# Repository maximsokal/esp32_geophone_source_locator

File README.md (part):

# ESP32 Geophone Source Locator

ESP32-S3 diploma prototype for seismic search under rubble. The firmware acquires multiple geophone channels simultaneously, stores object/measurement data on microSD, exposes a local web interface, provides a local TFT UI, and now contains a reusable 3D TDOA geometry solver for the later localization pipeline.

The project targets **ESP-IDF v5.5.4** on an ESP32-S3 N16R8 board.

For the component/runtime design, task ownership and extension rules, see [ARCHITECTURE.md](ARCHITECTURE.md).

Structural code search and linting use [ast-grep](docs/ast-grep.md).

## Current hardware architecture

### ESP32-S3

The controller is an ESP32-S3 with 16 MB flash and 8 MB octal PSRAM.

PSRAM runs at 80 MHz. If the board is unstable (random crashes after a ~20 °C temperature change or boot failures), revert to `CONFIG_SPIRAM_SPEED_40M`; HIL validation is required.

GPIO33-GPIO37 are occupied by octal PSRAM internally and are intentionally not assigned to application peripherals.

### SPI2: UI and storage

SPI2 is shared only by the TFT and microSD card:

| Signal | ESP32-S3 GPIO |
| --- | ---: |
| MOSI | 11 |
| SCLK | 12 |
| MISO | 13 |
| TFT CS | 14 |
| TFT DC | 15 |
| TFT RESET | 16 |
| microSD CS | 17 |

The current firmware sets the microSD SPI runtime ceiling to **20 MHz** (`SDMMC_FREQ_DEFAULT`); discovery starts at 400 kHz. This is the configured ceiling, not a claim that the present wiring has been physically validated at that rate.

### SPI3: dedicated AD7606 acquisition bus

AD7606 is isolated from the display/storage bus and owns SPI3:

| AD7606 signal | ESP32-S3 GPIO |
| --- | ---: |
| DOUTA / DB7 / MISO | 39 |
| RD / SCLK | 40 |
| CS | 41 |
| CONVST A + CONVST B | 42 |
| BUSY | 47 |
| RST | 2 |

AD7606 serial mode is read-only, therefore SPI3 MOSI is unused. A 10 kOhm pull-up is used on AD7606 CS.

Current AD7606 board configuration:

- RANGE low: +/-5 V input range;
- OS0/OS1/OS2 low: no hardware oversampling;
- 8 simultaneous channels;
- SPI mode 2;
- 1 MHz SPI clock;
- default acquisition rate: 500 Hz.

The first four AD7606 channels currently feed the application seismic ring buffer. All eight channels are read on every conversion and are available to the local TFT diagnostics UI.

### Other current GPIO assignments

| Function | GPIO |
| --- | ---: |
| Analog keypad KS0466 | 8 |
| Pololu power-off control | 18 |
| External power-button sense | 21 |

GPIO1 is reserved by the existing divider/bench wiring and must not be reused for AD7606.

### nRF54L15 subproject

`nRF54L15/` is an independent PlatformIO + Zephyr project for all XIAO
nRF54L15 nodes. It has one production source tree, one production environment
and one firmware binary; runtime topology and Bluetooth initiator/reflector
roles do not create central/remote builds. The main node is on the ESP32-S3
upstream I2C bus; remote nodes are behind TCA9548A channels. Each remote nRF
locally aggregates its GY-BMI160 and BME280 on the second XIAO I2C pair
(`D11/P0.03` SCL, `D12/P0.04` SDA), powered from XIAO `3V3_OUT`. These local
sensors are not direct ESP32/TCA devices. RJ45 pin 2 (+3.3 V) is reserved/NC
and must not be tied to `3V3_OUT`.

The installed boards are the **plain XIAO nRF54L15, not the Sense variant**,
so they have no built-in IMU. Each remote geophone uses an external
**GY-BMI160** and BME280 on the XIAO's private second I2C bus: `D11/P0.03` is
SCL and `D12/P0.04` is SDA. The upstream ESP32/TCA bus remains on
`D4/P1.10` SDA and `D5/P1.11` SCL. The main-enclosure nRF54L15 does not
require the remote-only sensor assembly.

The REMOTE logger LEDs show GREEN while READY when no fault has latched; GREEN
means “no latched fault,” not that sensor preparation has completed. An
unattempted sensor is pending, while a failed BMI160 or required BME280 init is
an immediate ERROR. Runtime IMU/ENV fault bits count only after that sensor is
READY. WARNING must persist for 2000 ms before YELLOW latches; ERROR/FATAL is
immediate, and latches clear only on reset. `LOG_RING_LOSS` latches WARNING
when `overwritten_total > 0` (internal logger losses also map to WARNING). The
128-record ring can overwrite during a bench run without an ESP32 collector,
producing a latched YELLOW; this is expected bench behavior.

The authoritative topology, local sensor/power contract, external
GY-BMI160/verticality contract, Channel Sounding role rotation and remote LED
pinout are in
[`ARCHITECTURE.md`](ARCHITECTURE.md). The future nRF implementation and
testing task is [`docs/nrf54l15-test-task.md`](docs/nrf54l15-test-task.md).

## UI architecture

The TFT UI uses **LVGL 9** through Espressif's official **esp_lvgl_port** integration. The display component is limited to the physical `esp_lcd` / ILI9341 layer; widgets, text, QR rendering, navigation, refresh timing and buffering belong to LVGL.

Managed dependencies are pinned through the ESP-IDF Component Manager:

- `espressif/esp_lcd_ili9341 ^2.0.2`;
- `espressif/esp_lvgl_port ^2.9.0`;
- `lvgl/lvgl ^9.5.0`;
- `espressif/button 4.2.0` for the keypad and power-button adapters;
- `espressif/i2c_bus 1.5.2` for the shared INA3221 sensor bus;
- `espressif/led_indicator 2.1.2` as the disabled, board-wiring-gated status backend;
- `espressif/esp-dsp 1.8.2` for the task-free measured-signal foundation;
- optional `espressif/esp_insights 1.3.4`, disabled in the baseline image.

The previous project-local 5x7 bitmap font and custom text-rendering stack are no longer part of the active display architecture.

The LVGL handler task is pinned to **Core 0**. The five-button analog keypad
uses official ADC Button objects over the existing ADC1 owner, and the GPIO21
power input uses the official GPIO Button object with external pull circuitry.
Both adapters publish to the dedicated ESP-IDF `APP_EVENT` user loop; the UI
subscriber only queues events and applies them from the existing LVGL timer.
The event loop contract is documented in
[`ARCHITECTURE.md`](ARCHITECTURE.md), and the before/after resource snapshot is
in [`docs/architecture-refactor-baseline-2026-09-12.md`](docs/architecture-refactor-baseline-2026-09-12.md).

Screen behavior is registered through one `ui_screen_driver_t` table. Open/render/key/refresh behavior and the Home menu label therefore have one source of truth instead of duplicated enum/switch routing.

Current screens:

- Home;
- Objects;
- Measurements;
- Storage;
- Wi-Fi / Web;
- System.

The **Measurements** screen is live, not a placeholder. For the AD7606 build it displays:

- acquisition source and RUN/STOP state;
- sample rate and channel count;
- real-time core assignment;
- SPI3 transport, SPI mode and bus clock;
- configured +/-5 V range and hardware oversampling ratio;
- successful sample count, read errors and consecutive failures;
- age of the last simultaneous sample;
- live V1..V8 values in mV.

The UI consumes a read-only `seismic_acquisition_snapshot_t`; it does not access AD7606 GPIO or SPI functions directly.

## CPU/task policy

Application-owned tasks are split by role.

### Core 0 - services

- LVGL handler and bounded UI event application;
- ESP-IDF `APP_EVENT` user loop and official Button service;
- object service;
- storage service;
- Wi-Fi/HTTP-facing application work.

### Core 1 - real-time side

- AD7606 acquisition;
- synthetic seismic test source;
- future signal preprocessing / event detection;
- future continuous localization worker if required.

All application task priorities, stacks and core assignments are centralized in `components/app_config/include/app_task_config.h`.

The AD7606 task initializes and owns SPI3 on Core 1 so the dedicated acquisition bus and its interrupt affinity remain on the real-time side.

## Seismic acquisition pipeline

For the AD7606 source:

```text
geophone
   -> low-noise analog amplifier/filter
   -> AD7606 simultaneous analog inputs
   -> CONVST
   -> timestamp captured at the sampling event
   -> BUSY completion
   -> SPI3 read of V1..V8
   -> acquisition diagnostics snapshot
   -> seismic ring buffer
   -> web / recording / future signal processing
```

The frame timestamp is captured immediately after the CONVST rising edge, not after BUSY handling and SPI transfer.

The seismic ring buffer uses short metadata critical sections plus per-slot publication sequencing. HTTP snapshots do not hold a long mutex while copying hundreds of waveform frames, so a slow web reader does not block the acquisition producer for the duration of the copy.

## Acquisition source interface

The source is selected at build time in `menuconfig`:

- `AD7606 SPI acquisition` - normal hardware path;
- `Synthetic test waveform` - software-only waveform source.

Each backend implements the same private `seismic_source_driver_t` interface. The acquisition orchestrator itself is backend-agnostic; compile-time selection is isolated in the source registry. Runtime source switching is intentionally not exposed yet.

Current backend files:

- `seismic_source_ad7606.c`;
- `seismic_source_test.c`.

Adding a new source should add a descriptor and registry entry rather than adding source-specific branches to `seismic_acquisition.c`.

## TDOA localization component

The repository now contains an independent `localization` component with a reusable 3D TDOA solver:

```c
esp_err_t localization_tdoa_solve(...);
```

It accepts:

- 4..8 sensor positions in meters;
- one arrival timestamp per sensor for the same detected event;
- a propagation speed in m/s;
- an optional initial source-position guess.

It returns:

- estimated `(x, y, z)` source position;
- estimated emission time;
- RMS timing residual;
- iteration count;
- convergence status.

The solver rejects degenerate/coplanar 3D sensor geometry and uses damped nonlinear least-squares iterations.

Beside it, `localization_velocity_free` provides three methods that estimate the event's own velocity: **TDCAS** (P picks, 6 sensors or 5 on a flat array), **PSAFUVS** (P and S picks, 4 flat sensors suffice) and **SUEA** (shortest travel paths around empty areas). "Calculate source" runs all of them; when the session has a registered 3D scan, their scan-constrained variants use the scan's empty (FREE) and filled (OCCUPIED) space. See [ARCHITECTURE.md](ARCHITECTURE.md#velocity-free-methods-and-the-3d-scans-emptyfilled-space).

`localization_extended` adds five more: **cross-correlation TDOA** over every pod pair, a **robust** outlier-rejecting fit, **PSP** (P-TDOA and S-P jointly), **eikonal** travel times that go around the scan's voids (plus tomography from calibration hits), and a **Bayesian** posterior that reports a 90% credible region instead of a bare point. With four flat pods, place them off a common circle (not in a rectangle) if you want the velocity-free methods. See [ARCHITECTURE.md](ARCHITECTURE.md#extended-methods-waveform-delays-robust-fits-p-s-eikonal-posterior).

**Important:** this does not mean the end-to-end locator is finished. The firmware still needs a validated preprocessing/event-detection stage that converts raw geophone data into reliable per-channel arrival timestamps. The propagation speed also cannot be hard-coded as a universal constant for heterogeneous rubble; `localization_default_config()` deliberately leaves `propagation_speed_mps` unset so the caller must provide a measured or modelled value.

Planned end-to-end path:

```text
AD7606 frames
   -> filtering / preprocessing
   -> event detection
   -> per-channel arrival-time picking
   -> sensor position / height data
   -> propagation model
   -> localization_tdoa_solve()
   -> source position + residual / quality
```

## Current timing limitation

Timestamp placement is already correct: timestamps represent CONVST, not later SPI completion.

The periodic trigger is still initiated by `esp_timer` + task notification. That is acceptable for the current bench stage, but it is not claimed to be the final deterministic sampling architecture. If the later TDOA error budget shows scheduler/trigger jitter to be significant, CONVST timing must move to a hardware-timed path rather than merely changing where software reads a timestamp.

## Storage and safe shutdown

Object and measurement state is stored under `/sdcard/geolocator`.

The shutdown sequence stops producers/services before cutting power:

```text
official Button adapters / shutdown latch
-> INA3221 monitor
-> shared sensor_bus / I2C0 release
-> measurement service / recorder finalization (LVGL guard still alive)
-> APP_EVENT UI subscriber / LVGL port
-> storage service
-> object service
-> seismic acquisition
-> HTTP / Wi-Fi
-> storage manager
-> SD unmount
-> display disable/deinit
-> power-off pulse
```

The SD handle is cleared only after successful FAT unmount. If unmount fails, software state still reflects that the card handle is present.

The TFT Storage screen requires a second confirmation before application-data erase is started.

## Web interface

The firmware starts a local HTTPS server on port 443 (`https://geolocator.local/`) and exposes device/seismic APIs including:

- `/api/status`
- `/api/seismic`

`/api/seismic` can return recent waveform frames without holding the acquisition producer behind a long reader-side copy.

The web component exposes only `include/web_server.h` publicly. Internal routes, JSON helpers, setup parsing and static-asset declarations share one private `web_server_internal.h` instead of a separate private header for every `.c` file.

## Build

For local firmware tests, the risk-based coverage plan and host/target verification boundaries, see [docs/firmware-test-plan.md](docs/firmware-test-plan.md). The project-wide validation contract, including the staged nRF54L15 software/HIL gates, is [docs/local-verification.md](docs/local-verification.md).

The sensor input/output map and its offline executable checks are in [docs/sensor-signals.md](docs/sensor-signals.md): `python tools/run_sensor_signal_checks.py`.

Install ESP-IDF v5.5.4 and open an ESP-IDF terminal in the repository directory.

When managed dependencies change:

```powershell
idf.py reconfigure
```

Build:

```powershell
idf.py build
```

Select another seismic backend:

```powershell
idf.py menuconfig
```

Then open **Seismic Acquisition** and select the required source.

## Flash and monitor

For repeatable local verification, use the tasks in `.vscode/tasks.json`:

* `Tests: nRF54L15` launches the isolated path-safe PlatformIO/Zephyr automatic
  software-test action through `nRF54L15/pio.ps1` without uploading a test
  image. Only explicitly qualified `test_sw_*` suites belong to this path.
* `nRF54L15: Flash firmware` builds and uploads the nRF54L15 image through
  `nRF54L15/pio.ps1`; it is a physical-board action and is not part of
  `Tests: All (no flash)`.
* `Tests: All (no flash)` is the no-flash project-wide entry point. It includes
  the nRF54L15 wrapper build and only qualified nRF software/native tests; an
  empty current `test_sw_*` surface is reported as `SKIPPED`. Physical nRF
  target/HIL suites are excluded even though PlatformIO also supports embedded
  tests.
* `ESP: Unity tests (flash COM4 + logs COM6)` runs the target Unity cases with
  a live COM4 preflight, an explicit test-app flash, and a bounded COM6 log
  capture.
* `ESP: Production pipeline HIL (COM4 + COM6)` builds the production image,
  prompts for the HTTPS base URL and an existing object ID, then runs the live
  acquisition/recorder/API gate with explicit COM4 flash and COM6 logging.
* `ESP: Flash production (COM4)` and `ESP: Monitor logs (COM6)` remain separate
  tasks for production firmware, each with its matching live-port preflight.
* `ESP-IDF: Monitor + Save Logs` lets you choose a COM port and keeps one UTF-8
  capture file in `logs/esp32/` while waiting through startup port errors and
  USB reconnects. `RUNNING` appears after UART data arrives. Stop the active
  monitor with `Ctrl+]`, or use `Ctrl+C` while it is retrying the connection.

For the keypad ADC/timer-task watchlist, use the dedicated opt-in procedure in
[docs/keypad-adc-timing-hil.md](docs/keypad-adc-timing-hil.md). It measures
broker snapshot `min/avg/p95/max` and shared `ESP_TIMER_TASK` dispatch lateness
for separate AD7606 500 Hz windows; it does not change the
production defaults. Its `KEYPAD_TIMING_TELEMETRY_RESULT` confirms only
telemetry validity and is independent of the physical keypad condition;
`PHYSICAL_CONDITION` and `KEYPAD_TIMING_RUN_RESULT` report the separate HIL
gate. Performance acceptance remains `NOT_ESTABLISHED` until real-board
baselines define thresholds.

The host contracts cover the AD7606 DMA configuration; the production HIL
runner reports AD7606 startup, configured-rate frame cadence, recorder/session
metadata, exact seismic channel IDs and bounded timestamp jitter,
`/api/seismic`/`/api/status` checks (including zero AD7606 read errors and
consecutive failures) and advancing FreeRTOS heartbeats for the
acquisition, recorder and UI loops. The official Button component owns input
sampling/debounce; its physical delivery and electrical behavior are checked
separately during HIL. During recording it
also requires acquisition and recorder progress to advance. It uses the device
monotonic `runtime.now_ms` to reject task heartbeats older than the configured
`-MaxTaskHeartbeatAgeMs` (default 1000 ms). TFT pixels and
keypad/power-button responsiveness still require a human observation during the
live Measurements run; use `-RequireFullPipeline` so missing API, SD or physical
evidence is reported as `BLOCKED` instead of being mistaken for a complete pass.
After observing the live screen, keypad navigation and ordered shutdown, repeat
the explicit command with `-ConfirmTftRendering -ConfirmKeypadResponsive
-ConfirmPowerButtonResponsive` to record those three manual attestations as
`PASS`.

Use the board programming port for flashing:

```powershell
idf.py -p COM4 flash
```

In the current bench setup an external USB-to-TTL adapter can be used as a passive UART monitor while the device runs from the 2x18650 power system. The external adapter must not power the ESP32 board.

Typical passive monitor wiring:

```text
ESP32 GPIO43 TX -> USB-TTL RXD
ESP32 GND       -> USB-TTL GND
```

USB-TTL TXD and power pins are not required for log-only monitoring.

Example:

```powershell
idf.py -p COM6 monitor
```

COM numbers are development-machine specific.

## Hardware bring-up checks

A normal AD7606 start should contain messages equivalent to:

```text
AD7606_DRIVER: GPIO configured: RESET=2 CONVST=42 BUSY=47 CS=41
AD7606_DRIVER: Initializing dedicated SPI3: MISO=39 SCLK=40
AD7606_DRIVER: SPI3 initialized successfully: DMA=auto (SPI_DMA_CH_AUTO)
AD7606_DRIVER: Self-test conversion + SPI read OK
AD7606_ACQ: Started: 500 Hz, 8 channels, SPI3 dedicated, core=1
```

For a known approximately 1.6 V divider connected to V8, a representative reading is around:

```text
raw=[...,10500]
mV=[...,1602]
```

The same V8 value should appear on the LVGL Measurements screen. Exact values depend on the measured supply/reference/input voltage and must not be treated as a calibration result.

## Open-source components and original work

### Open-source components

#### ESP32-S3 and ESP-IDF components

| Component | Version | SPDX license | Source | Usage |
| --- | --- | --- | --- | --- |
| ESP-IDF | 5.5.4 | [Apache-2.0](https://spdx.org/licenses/Apache-2.0.html) | [espressif/esp-idf](https://github.com/espressif/esp-idf) | External framework and build tools for ESP32-S3 firmware. |
| `espressif/button` | 4.2.0 | [Apache-2.0](https://spdx.org/licenses/Apache-2.0.html) | [esp-iot-solution/button](https://github.com/espressif/esp-iot-solution/tree/master/components/button) | Keypad and power button: `components/keypad`, `components/power_control`. |
| `espressif/cbor` | 0.6.1~4 | [MIT](https://spdx.org/licenses/MIT.html) | [idf-extra-components/cbor](https://github.com/espressif/idf-extra-components/tree/master/cbor) | Transitive ESP Insights dependency. |
| `espressif/cmake_utilities` | 0.5.3 | [Apache-2.0](https://spdx.org/licenses/Apache-2.0.html) | [esp-iot-solution/cmake_utilities](https://github.com/espressif/esp-iot-solution/tree/master/tools/cmake_utilities) | Transitive build helper. |
| `espressif/esp-dsp` | 1.8.2 | [Apache-2.0](https://spdx.org/licenses/Apache-2.0.html) | [espressif/esp-dsp](https://github.com/espressif/esp-dsp) | Declared but unused; intentionally retained and pinned by the architecture contract test (`tests/python/test_architecture_refactor_contract.py`). |
| `espressif/esp_diag_data_store` | 1.1.1 | [Apache-2.0](https://spdx.org/licenses/Apache-2.0.html) | [esp-insights/esp_diag_data_store](https://github.com/espressif/esp-insights/tree/main/components/esp_diag_data_store) | Transitive ESP Insights dependency. |
| `espressif/esp_diagnostics` | 1.3.4 | [Apache-2.0](https://spdx.org/licenses/Apache-2.0.html) | [esp-insights/esp_diagnostics](https://github.com/espressif/esp-insights/tree/main/components/esp_diagnostics) | Transitive ESP Insights dependency. |
| `espressif/esp_insights` | 1.3.4 | [Apache-2.0](https://spdx.org/licenses/Apache-2.0.html) | [esp-insights/esp_insights](https://github.com/espressif/esp-insights/tree/main/components/esp_insights) | Optional `components/insights_bridge` component; disabled in the current `sdkconfig`. |
| `espressif/esp_lcd_ili9341` | 2.0.2 | [Apache-2.0](https://spdx.org/licenses/Apache-2.0.html) | [esp-bsp/esp_lcd_ili9341](https://github.com/espressif/esp-bsp/tree/master/components/lcd/esp_lcd_ili9341) | TFT driver in `components/display`. |
| `espressif/esp_lvgl_port` | 2.9.0 | [Apache-2.0](https://spdx.org/licenses/Apache-2.0.html) | [esp-bsp/esp_lvgl_port](https://github.com/espressif/esp-bsp/tree/master/components/esp_lvgl_port) | LVGL integration for the TFT. |
| `espressif/i2c_bus` | 1.5.2 | [Apache-2.0](https://spdx.org/licenses/Apache-2.0.html) | [esp-iot-solution/i2c_bus](https://github.com/espressif/esp-iot-solution/tree/master/components/i2c_bus) | Shared sensor bus and barometer/nRF topology services. |
| `espressif/led_indicator` | 2.1.2 | [Apache-2.0](https://spdx.org/licenses/Apache-2.0.html) | [esp-iot-solution/led_indicator](https://github.com/espressif/esp-iot-solution/tree/master/components/led/led_indicator) | Indicator adapter; the current board driver is disabled. |
| `espressif/led_strip` | 3.0.3 | [Apache-2.0](https://spdx.org/licenses/Apache-2.0.html) | [idf-extra-components/led_strip](https://github.com/espressif/idf-extra-components/tree/master/led_strip) | Transitive LED dependency. |
| `espressif/mdns` | 1.11.3 | [Apache-2.0](https://spdx.org/licenses/Apache-2.0.html) | [esp-protocols/mdns](https://github.com/espressif/esp-protocols/tree/master/components/mdns) | mDNS in `components/wifi_manager`. |
| `espressif/rmaker_cmd_resp` | 1.0.0 | [Apache-2.0](https://spdx.org/licenses/Apache-2.0.html) | [esp-rainmaker-common/rmaker_cmd_resp](https://github.com/espressif/esp-rainmaker-common/tree/master/components/rmaker_cmd_resp) | Transitive ESP Insights dependency. |
| `espressif/rmaker_common` | 1.8.6 | [Apache-2.0](https://spdx.org/licenses/Apache-2.0.html) | [esp-rainmaker-common](https://github.com/espressif/esp-rainmaker-common) | Transitive ESP Insights dependency. |
| `espressif/rmaker_common_events` | 1.0.0 | [Apache-2.0](https://spdx.org/licenses/Apache-2.0.html) | [esp-rainmaker-common/rmaker_common_events](https://github.com/espressif/esp-rainmaker-common/tree/master/components/rmaker_common_events) | Transitive ESP Insights dependency. |
| `espressif/rmaker_console` | 1.0.1 | [Apache-2.0](https://spdx.org/licenses/Apache-2.0.html) | [esp-rainmaker-common/rmaker_console](https://github.com/espressif/esp-rainmaker-common/tree/master/components/rmaker_console) | Transitive ESP Insights dependency. |
| `espressif/rmaker_system_ctrl` | 1.0.0 | [Apache-2.0](https://spdx.org/licenses/Apache-2.0.html) | [esp-rainmaker-common/rmaker_system_ctrl](https://github.com/espressif/esp-rainmaker-common/tree/master/components/rmaker_system_ctrl) | Transitive ESP Insights dependency. |
| `espressif/rmaker_time_sync` | 1.0.2 | [Apache-2.0](https://spdx.org/licenses/Apache-2.0.html) | [esp-rainmaker-common/rmaker_time_sync](https://github.com/espressif/esp-rainmaker-common/tree/master/components/rmaker_time_sync) | Transitive ESP Insights dependency. |
| `espressif/rmaker_work_queue` | 1.0.0 | [Apache-2.0](https://spdx.org/licenses/Apache-2.0.html) | [esp-rainmaker-common/rmaker_work_queue](https://github.com/espressif/esp-rainmaker-common/tree/master/components/rmaker_work_queue) | Transitive ESP Insights dependency. |
| `lvgl/lvgl` | 9.6.0~1 | [MIT](https://spdx.org/licenses/MIT.html) | [lvgl/lvgl](https://github.com/lvgl/lvgl) | UI in `components/ui`, QR widget, and TFT fonts. |
| Montserrat Regular for LVGL | commit `cc8daf2e7085006b9c112542fc82b58afc13521d` | [OFL-1.1](https://spdx.org/licenses/OFL-1.1.html) | [JulietaUla/Montserrat](https://github.com/JulietaUla/Montserrat) | TTF SHA-256: `3e8abe50c44c82e2242e97d1ec8c0d385c4890cdc50447bcdb8605c81a38cfb2`; embedded LVGL font version 9.000; license is retained in `components/ui/fonts/OFL.txt`. |
| QR-Code-generator by Project Nayuki in LVGL | Version not pinned separately; included in LVGL 9.6.0~1 | [MIT](https://spdx.org/licenses/MIT.html) | [Nayuki QR Code generator](https://www.nayuki.io/page/qr-code-generator-library) | `lv_qrcode` widget engine for Wi-Fi QR codes on the TFT; source and license are included in LVGL. |
| Built-in LVGL Montserrat / Font Awesome glyphs | LVGL 9.6.0~1; Font Awesome version not pinned | [OFL-1.1](https://spdx.org/licenses/OFL-1.1.html) for font glyphs; [CC-BY-4.0](https://spdx.org/licenses/CC-BY-4.0.html) for Font Awesome icons | [LVGL](https://github.com/lvgl/lvgl), [Font Awesome](https://fontawesome.com) | Built-in `LV_SYMBOL_*` symbols in the TFT UI. |

#### Libraries bundled with ESP-IDF

| Component | Version | SPDX license | Source | Usage |
| --- | --- | --- | --- | --- |
| cJSON | 1.7.19 | [MIT](https://spdx.org/licenses/MIT.html) | [DaveGamble/cJSON](https://github.com/DaveGamble/cJSON) | JSON support in `object_store`, `localization_results`, `web_server`, and `workflow_service`. |
| FreeRTOS-Kernel | 10.5.1 | [MIT](https://spdx.org/licenses/MIT.html) | [FreeRTOS/FreeRTOS-Kernel](https://github.com/FreeRTOS/FreeRTOS-Kernel) | Firmware task and queue kernel. |
| Mbed TLS | 3.6.5 | [Apache-2.0](https://spdx.org/licenses/Apache-2.0.html) OR [GPL-2.0-or-later](https://spdx.org/licenses/GPL-2.0-or-later.html) | [Mbed-TLS/mbedtls](https://github.com/Mbed-TLS/mbedtls) | ESP-TLS and HTTPS. |
| lwIP | 2.2.0, development snapshot | [BSD-3-Clause](https://spdx.org/licenses/BSD-3-Clause.html) | [lwip-tcpip/lwip](https://github.com/lwip-tcpip/lwip) | ESP-NETIF/Wi-Fi network stack. |
| FatFs | R0.15 patch 2 | [BSD-3-Clause](https://spdx.org/licenses/BSD-3-Clause.html) | [FatFs](http://elm-chan.org/fsw/ff/) | microSD file system in `components/sd_card`. |
| http-parser | 2.7.0 | [MIT](https://spdx.org/licenses/MIT.html) | [nodejs/http-parser](https://github.com/nodejs/http-parser) | ESP-IDF HTTP server in `components/web_server`. |
| wpa_supplicant | 2.10 | [BSD-3-Clause](https://spdx.org/licenses/BSD-3-Clause.html) | [w1.fi/wpa_supplicant](https://w1.fi/wpa_supplicant/) | Wi-Fi authentication. |
| protobuf-c | 1.4.1 | [MIT](https://spdx.org/licenses/MIT.html) | [protobuf-c/protobuf-c](https://github.com/protobuf-c/protobuf-c) | Transitive dependency of optional ESP Insights diagnostics. |
| SPIFFS | `0.2-255-g0dbb3f71c5f6`, listed in ESP-IDF v5.5.4 `.gitmodules`; not checked locally | [MIT](https://spdx.org/licenses/MIT.html) | [pellepl/spiffs](https://github.com/pellepl/spiffs) | Enabled in `sdkconfig`; no application API calls were found. |
| ESP-IDF Wi-Fi and PHY binary libraries | 5.5.4 | [Apache-2.0](https://spdx.org/licenses/Apache-2.0.html) | [ESP-IDF v5.5.4 components](https://github.com/espressif/esp-idf/tree/v5.5.4/components) | Closed-source SDK binaries for Wi-Fi and PHY. |

#### nRF54L15 / NCS

| Component | Version | SPDX license | Source | Usage |
| --- | --- | --- | --- | --- |
| nRF Connect SDK / `sdk-nrf` | v3.4.0 | [LicenseRef-Nordic-5-Clause](https://github.com/nrfconnect/sdk-nrf/blob/v3.4.0/nrf/LICENSE) | [nrfconnect/sdk-nrf](https://github.com/nrfconnect/sdk-nrf) | External SDK pinned in `nRF54L15/ncs.ps1`. |
| Zephyr fork in NCS | `ncs-v3.4.0` / Zephyr 4.4.0 | [Apache-2.0](https://spdx.org/licenses/Apache-2.0.html) | [nrfconnect/sdk-zephyr](https://github.com/nrfconnect/sdk-zephyr) | nRF54L15 kernel and Bluetooth stack. |
| nrfxlib / SoftDevice Controller | 3.4.0 | [LicenseRef-Nordic-5-Clause](https://github.com/nrfconnect/sdk-nrfxlib) | [nrfconnect/sdk-nrfxlib](https://github.com/nrfconnect/sdk-nrfxlib) | Bluetooth controller binary enabled in `prj.conf`. |
| hal_nordic | commit `18da0cc9726f8759c627dba3180b3ba9294e433c` | [BSD-3-Clause](https://spdx.org/licenses/BSD-3-Clause.html) for nrfx; [LicenseRef-Nordic-5-Clause](https://github.com/nrfconnect/sdk-nrf/blob/v3.4.0/nrf/LICENSE) for the module | [zephyrproject-rtos/hal_nordic](https://github.com/zephyrproject-rtos/hal_nordic) | Peripheral drivers. |
| CMSIS | commit `512cc7e895e8491696b61f7ba8066b4a182569b8` | [Apache-2.0](https://spdx.org/licenses/Apache-2.0.html) | [zephyrproject-rtos/cmsis](https://github.com/zephyrproject-rtos/cmsis) | Cortex-M core support. |

#### Web interface and asset packages

| Component | Version | SPDX license | Source | Usage |
| --- | --- | --- | --- | --- |
| `react` | 19.2.8 | [MIT](https://spdx.org/licenses/MIT.html) | [react/react](https://github.com/react/react) | UI runtime in `webui/src/main.tsx`; included in the WebUI package. |
| `react-dom` | 19.2.8 | [MIT](https://spdx.org/licenses/MIT.html) | [react/react](https://github.com/react/react) | Mounts the UI and reports; included in the WebUI package. |
| `three` | 0.185.1 | [MIT](https://spdx.org/licenses/MIT.html) | [mrdoob/three.js](https://github.com/mrdoob/three.js) | 3D rendering and scene controls. |
| `@react-three/fiber` | 9.7.0 | [MIT](https://spdx.org/licenses/MIT.html) | [pmndrs/react-three-fiber](https://github.com/pmndrs/react-three-fiber) | 3D point-cloud, scene, and localization views. |
| `js-aruco2` | 2.0.0 | [MIT](https://spdx.org/licenses/MIT.html) | [damianofalcioni/js-aruco2](https://github.com/damianofalcioni/js-aruco2) | AprilTag detector and JavaScript dictionary; included in the WebUI. |
| `@fontsource/montserrat` WOFF2 | 5.3.0 | [OFL-1.1](https://spdx.org/licenses/OFL-1.1.html) | [fontsource Montserrat](https://github.com/fontsource/font-files/tree/main/fonts/google/montserrat) | Latin and Cyrillic WOFF2 files are embedded in part of the WebUI package for report printing. |
| AprilTag `tag36h11` dictionary | Family version not pinned; dictionary data comes from `js-aruco2` 2.0.0 | [BSD-2-Clause](https://spdx.org/licenses/BSD-2-Clause.html) | [AprilRobotics/apriltag](https://github.com/AprilRobotics/apriltag) | Dictionary data in `webui/src/xr/fiducial/jsAruco2.ts`; no C AprilTag detector was found in the WebUI. |

#### Development and build tools

| Component | Version | SPDX license | Source | Usage |
| --- | --- | --- | --- | --- |
| `@types/react` | 19.2.18; manifest specifies `^19.2.0` | [MIT](https://spdx.org/licenses/MIT.html) | [DefinitelyTyped/types/react](https://github.com/DefinitelyTyped/DefinitelyTyped/tree/master/types/react) | Types for WebUI compilation. |
| `@types/react-dom` | 19.2.5; manifest specifies `^19.2.0` | [MIT](https://spdx.org/licenses/MIT.html) | [DefinitelyTyped/types/react](https://github.com/DefinitelyTyped/DefinitelyTyped/tree/master/types/react) | Types for WebUI compilation. |
| `@types/three` | 0.185.4 | [MIT](https://spdx.org/licenses/MIT.html) | [DefinitelyTyped/types/three](https://github.com/DefinitelyTyped/DefinitelyTyped/tree/master/types/three) | Types for WebUI compilation. |
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
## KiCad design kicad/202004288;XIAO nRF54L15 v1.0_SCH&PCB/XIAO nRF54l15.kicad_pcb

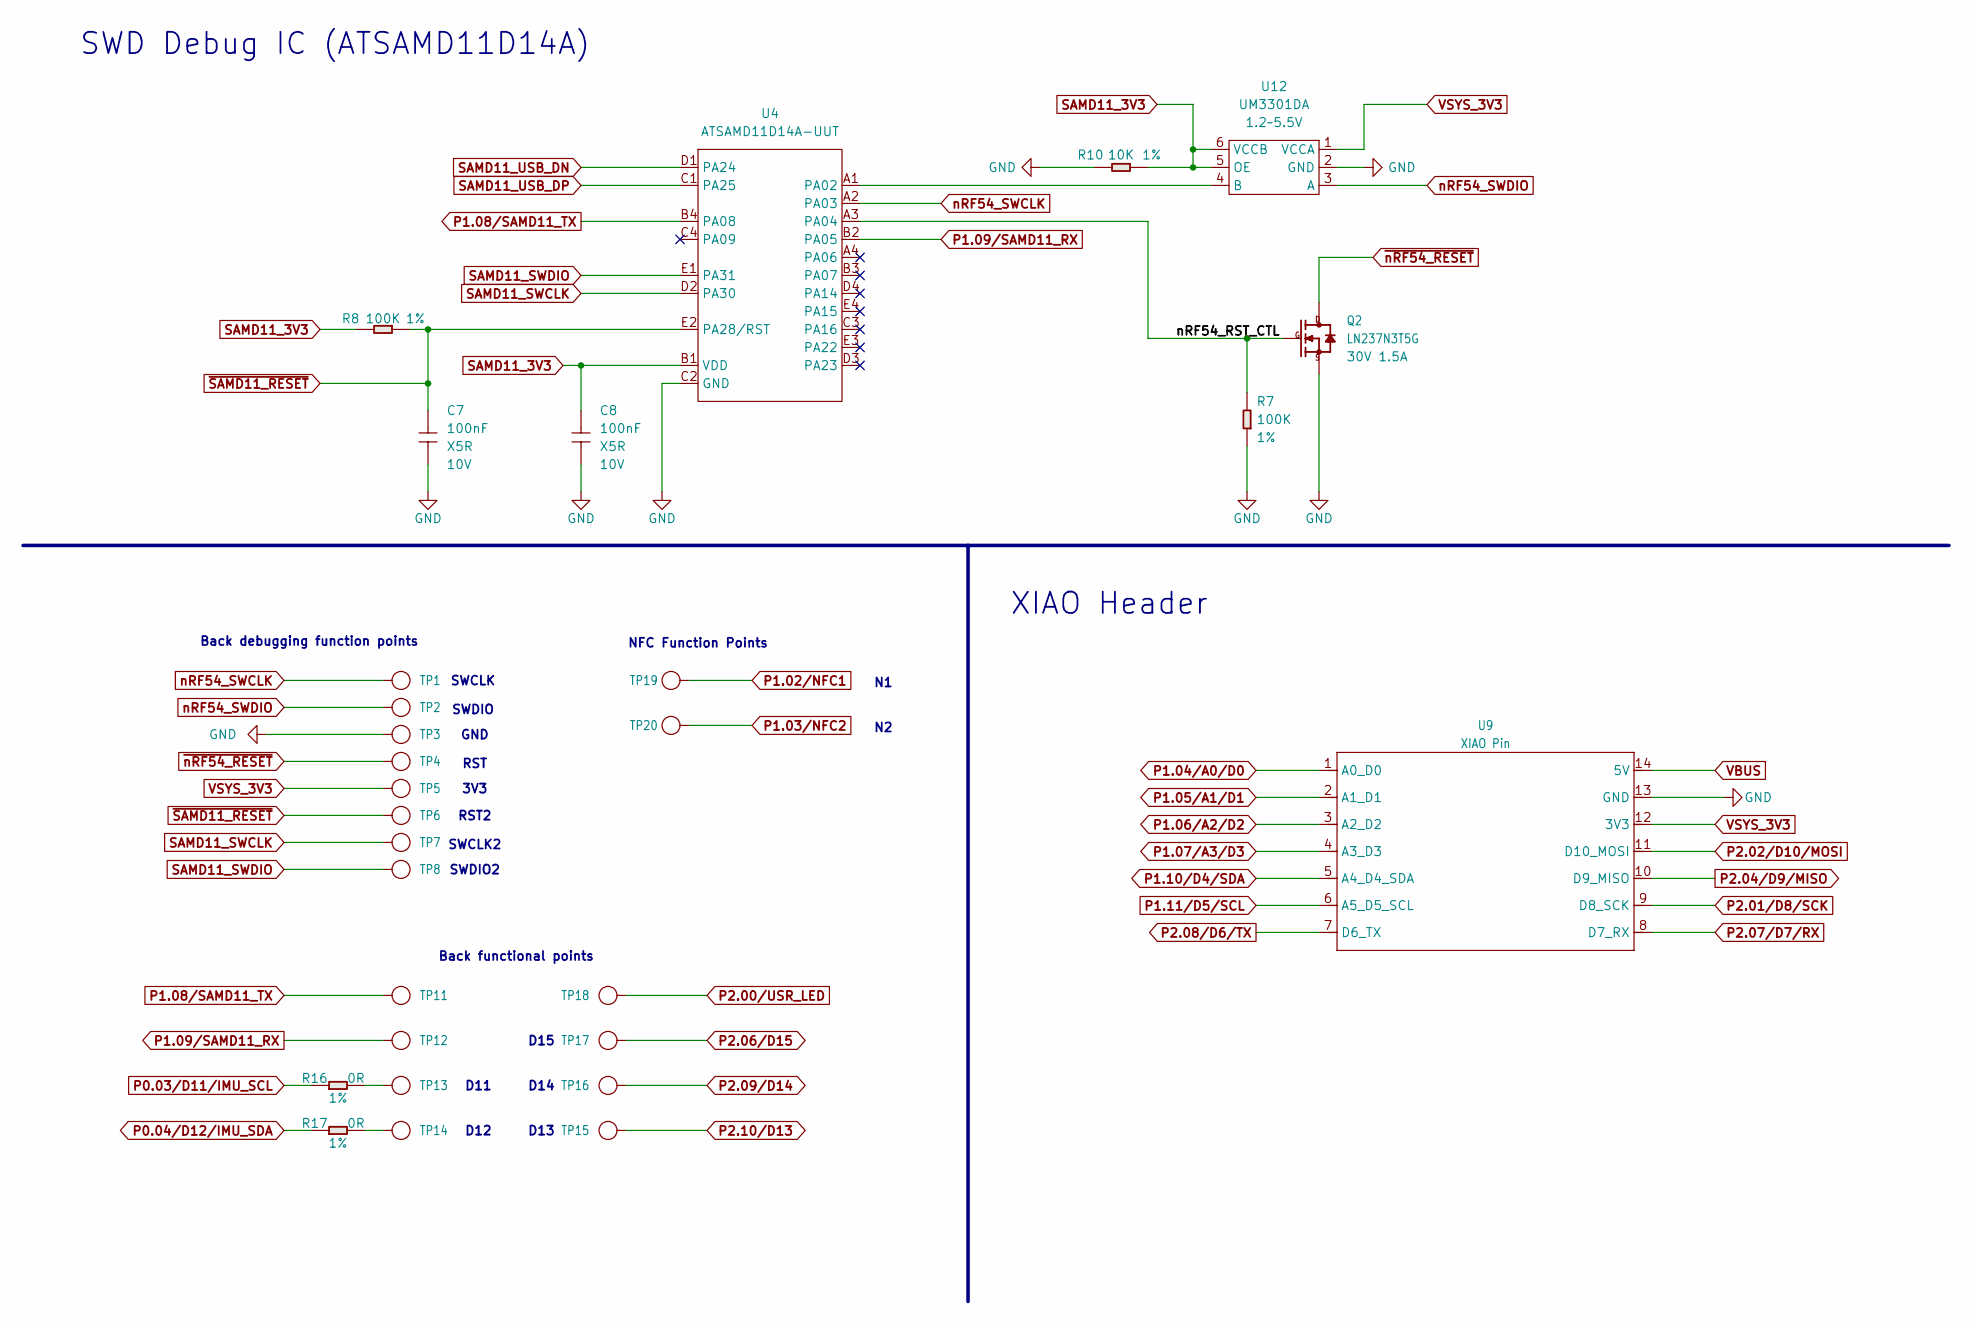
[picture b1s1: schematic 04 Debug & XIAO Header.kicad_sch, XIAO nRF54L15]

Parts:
C7, C8: 100nF; C0201; Voltage Rating 10V; MPN CC0201KRX5R6BB104
Q2: LN237N3T5G; PMOS_1.0X0.6X0.35MM; Rating 30V 1.5A; MPN LN237N3T5G
R7, R8: 100K; R0201; Power Rating 1%; MPN RC0201FR-07100KL
R10: 10K; R0201; Power Rating 1%; MPN RC0201FR-0710KL
R16, R17: 0R; R0201; Power Rating 1%; MPN RC0201FR-070RL
TP1, TP2, TP3, TP4, TP5, TP6, TP7, TP8: Test Point; TP-D45MIL; Part Type Test Point
TP11, TP12, TP13, TP14, TP15, TP16, TP17, TP18: Test Point; TP-1.6MM-ROUND; Part Type Test Point
TP19, TP20: Test Point; TP-80X40MIL; Part Type Test Point
U4: ATSAMD11D14A-UUT; WLCSP20-0.4-2.4X1.9X0.5MM_SMALL; MPN ATSAMD11D14A-UUT
U9: XIAO Pin; MOUDLE14P-XIAO-HALF-HOLE-PRO
U12: UM3301DA; DFN6-0.5-1.45X1X0.6; Rating 1.2~5.5V; MPN UM3301DA

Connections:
/04 Debug & XIAO Header/nRF54_RST_CTL: Q2.1 (G), R7.2, U4.A3 (PA04)
GND: C7.2, C8.2, Q2.2 (S), R7.1, R10.2, TP3.1 (T), U4.C2 (GND), U9.13 (GND), U12.2 (GND); also elsewhere on the board
unnamed: R16.2, TP13.1 (T)
unnamed: R17.2, TP14.1 (T)
unnamed: U4.A1 (PA02), U12.4 (B)
P0.03/D11/IMU_SCL: R16.1; also elsewhere on the board
P0.04/D12/IMU_SDA: R17.1; also elsewhere on the board
P1.02/NFC1: TP19.1 (T); also elsewhere on the board
P1.03/NFC2: TP20.1 (T); also elsewhere on the board
P1.04/A0/D0: U9.1 (A0_D0); also elsewhere on the board
P1.05/A1/D1: U9.2 (A1_D1); also elsewhere on the board
P1.06/A2/D2: U9.3 (A2_D2); also elsewhere on the board
P1.07/A3/D3: U9.4 (A3_D3); also elsewhere on the board
P1.08/SAMD11_TX: TP11.1 (T), U4.B4 (PA08); also elsewhere on the board
P1.09/SAMD11_RX: TP12.1 (T), U4.B2 (PA05); also elsewhere on the board
P1.10/D4/SDA: U9.5 (A4_D4_SDA); also elsewhere on the board
P1.11/D5/SCL: U9.6 (A5_D5_SCL); also elsewhere on the board
P2.00/USR_LED: TP18.1 (T); also elsewhere on the board
P2.01/D8/SCK: U9.9 (D8_SCK); also elsewhere on the board
P2.02/D10/MOSI: U9.11 (D10_MOSI); also elsewhere on the board
P2.04/D9/MISO: U9.10 (D9_MISO); also elsewhere on the board
P2.06/D15: TP17.1 (T); also elsewhere on the board
P2.07/D7/RX: U9.8 (D7_RX); also elsewhere on the board
P2.08/D6/TX: U9.7 (D6_TX); also elsewhere on the board
P2.09/D14: TP16.1 (T); also elsewhere on the board
P2.10/D13: TP15.1 (T); also elsewhere on the board
SAMD11_3V3: C8.1, R8.2, R10.1, U4.B1 (VDD), U12.5 (OE), U12.6 (VCCB); also elsewhere on the board
SAMD11_SWCLK: TP7.1 (T), U4.D2 (PA30)
SAMD11_SWDIO: TP8.1 (T), U4.E1 (PA31)
SAMD11_USB_DN: U4.D1 (PA24); also elsewhere on the board
SAMD11_USB_DP: U4.C1 (PA25); also elsewhere on the board
VBUS: U9.14 (5V); also elsewhere on the board
VSYS_3V3: TP5.1 (T), U9.12 (3V3), U12.1 (VCCA); also elsewhere on the board
nRF54_SWCLK: TP1.1 (T), U4.A2 (PA03); also elsewhere on the board
nRF54_SWDIO: TP2.1 (T), U12.3 (A); also elsewhere on the board
~SAMD11_RESET: C7.1, R8.1, TP6.1 (T), U4.E2 (PA28/RST)
~nRF54_RESET: Q2.3 (D), TP4.1 (T); also elsewhere on the board

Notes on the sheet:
Back functional points
D11
SWCLK2
XIAO Header
3V3
D12
SWDIO2
SWDIO
NFC Function Points
D15
SWCLK
D13
RST
Back debugging function points
SWD Debug IC (ATSAMD11D14A)
D14
RST2
GND

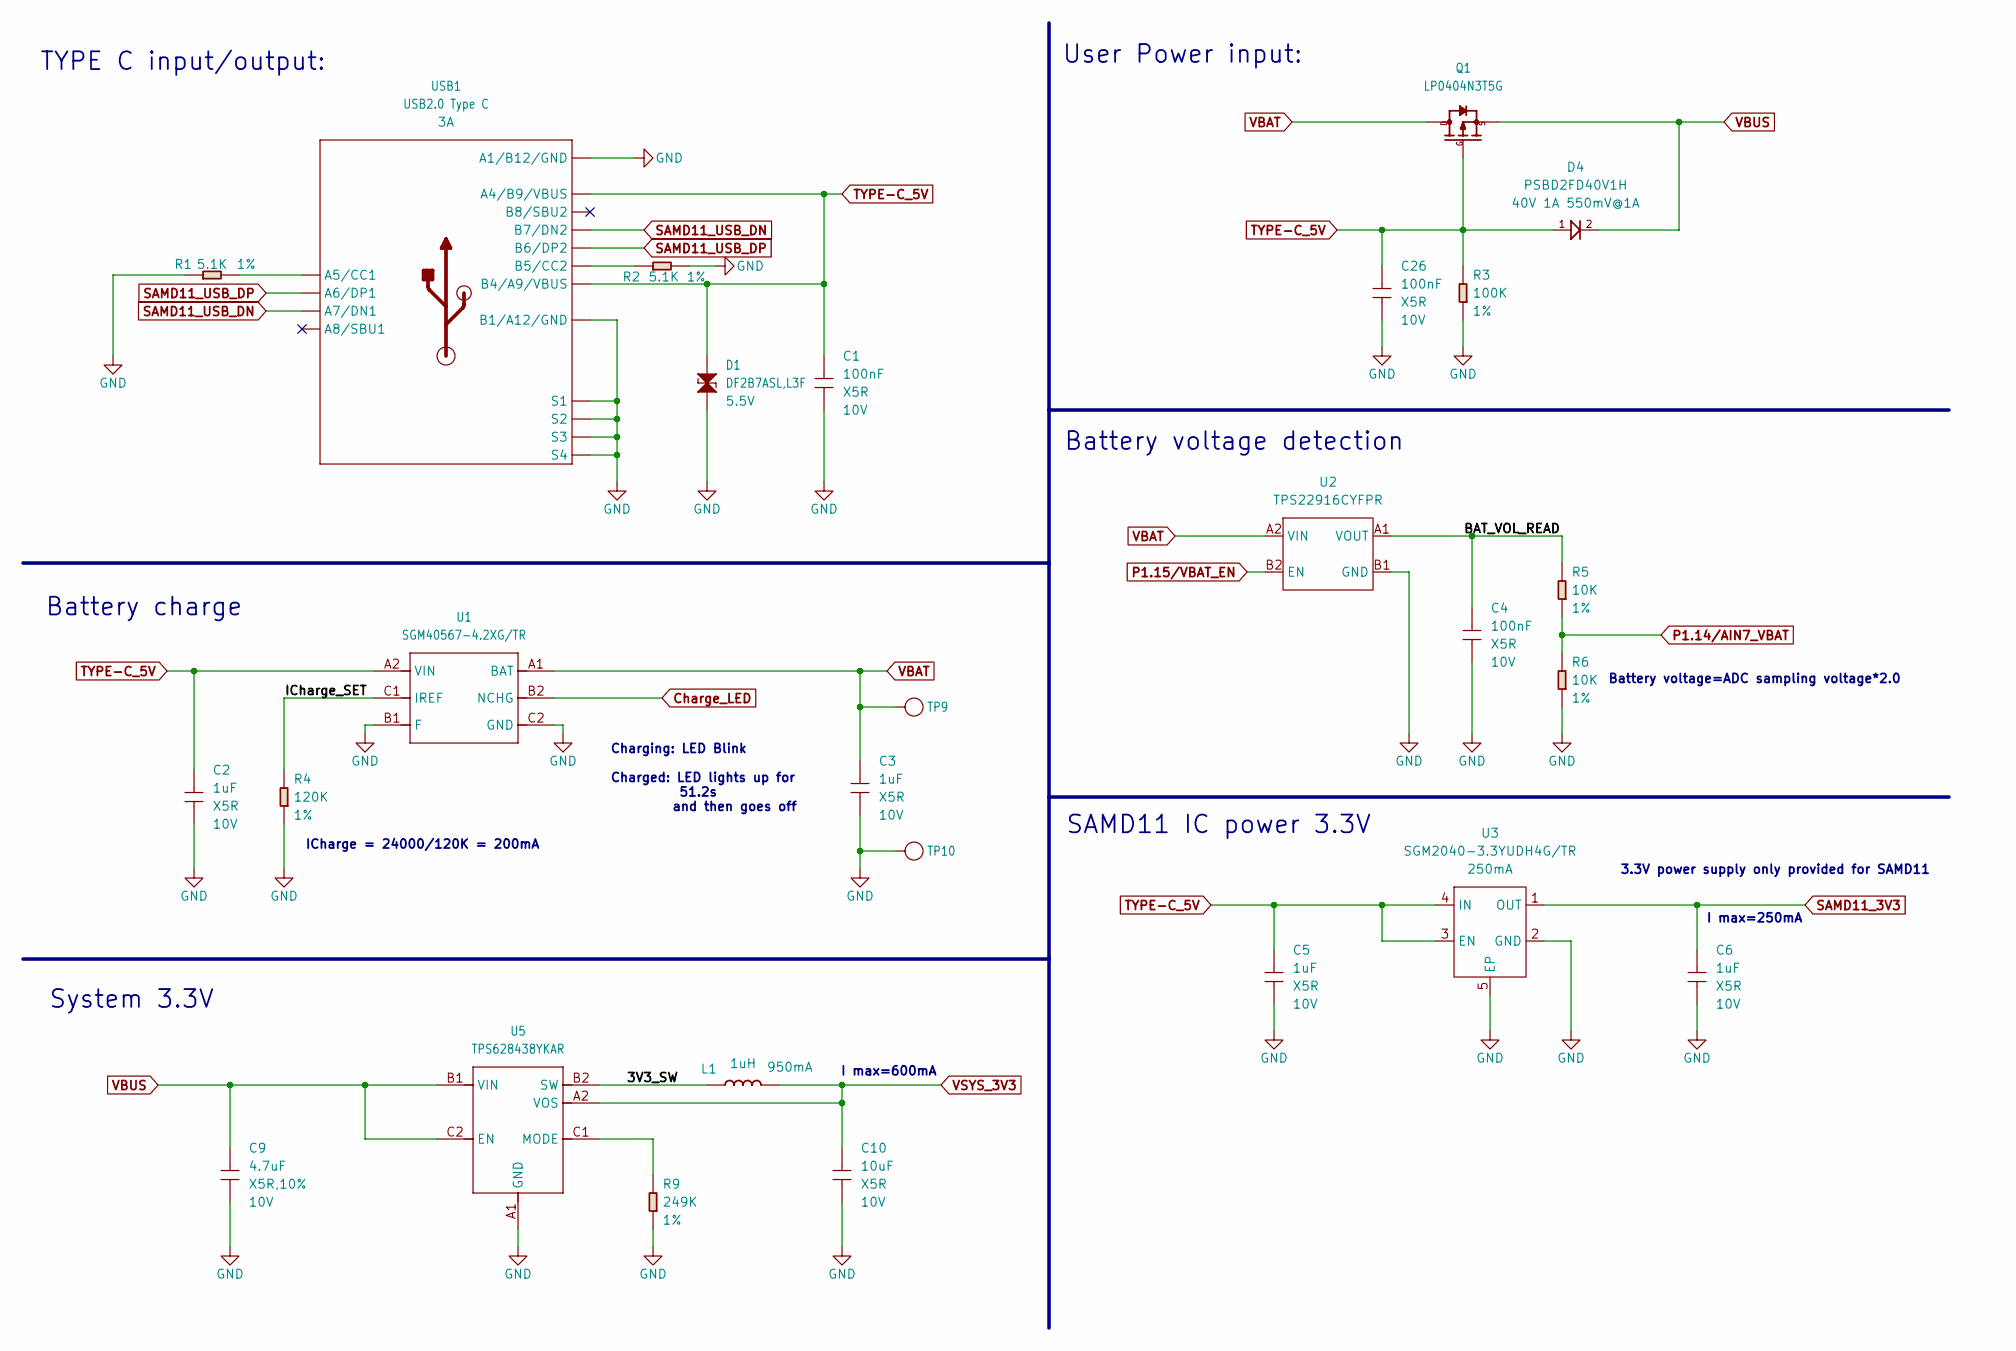
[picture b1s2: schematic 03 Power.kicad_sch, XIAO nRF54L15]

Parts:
C1, C4, C26: 100nF; C0201; Voltage Rating 10V; MPN CC0201KRX5R6BB104
C2, C3, C5, C6: 1uF; C0201; Voltage Rating 10V; MPN GRM033R61A105ME44D
C9: 4.7uF; C0402; Voltage Rating 10V; MPN CC0402KRX5R6BB475
C10: 10uF; C0402; Voltage Rating 10V; MPN CC0402MRX5R6BB106
D1: DF2B7ASL,L3F; ESD-0201; Rating 5.5V; MPN DF2B7ASL,L3F
D4: PSBD2FD40V1H; DFN1006-2L; Rating 40V 1A 550mV@1A; MPN PSBD2FD40V1H
L1: 1uH; L0603; Rating 950mA; MPN LQM18PN1R0MFRL
Q1: LP0404N3T5G; PMOS_1.0X0.6X0.35MM; MPN LP0404N3T5G
R1, R2: 5.1K; R0201; Power Rating 1%; MPN RC0201FR-075K1L
R3: 100K; R0201; Power Rating 1%; MPN RC0201FR-07100KL
R4: 120K; R0201; Power Rating 1%; MPN RC0201FR-07120KL
R5, R6: 10K; R0201; Power Rating 1%; MPN RC0201FR-0710KL
R9: 249K; R0201; Power Rating 1%; MPN RC0201FR-07249KL
TP9, TP10: Test Point; TP-80X40MIL; Part Type Test Point
U1: SGM40567-4.2XG/TR; WLCSP-0.4-0.92X1.16X0.4MM; MPN SGM40567-4.2XG/TR
U2: TPS22916CYFPR; WLCSP4-0.4-0.77X0.77X0.33MM; MPN TPS22916CYFPR
U3: SGM2040-3.3YUDH4G/TR; X2SON4-0.625-1x1x0.6mm; Rating 250mA; MPN SGM2040-3.3YUDH4G/TR
U5: TPS628438YKAR; BGA6-0.35-0.85X1.2X0.4MM; MPN TPS628438YKAR
USB1: USB2.0 Type C; USB2.0-TYPE-C_USB-31C-F-16P; Rating 3A; MPN ST-USB-3316T

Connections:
/03 Power/3V3_SW: L1.1, U5.B2 (SW)
/03 Power/BAT_VOL_READ: C4.1, R5.2, U2.A1 (VOUT)
/03 Power/ICharge_SET: R4.2, U1.C1 (IREF)
Charge_LED: U1.B2 (NCHG); also elsewhere on the board
GND: C1.2, C2.2, C3.2, C4.2, C5.2, C6.2, C9.2, C10.2, C26.2, D1.1, R1.1, R2.2, R3.1, R4.1, R6.1, R9.1, TP10.1 (T), U1.B1 (F), U1.C2 (GND), U2.B1 (GND), U3.2 (GND), U3.5 (EP), U5.A1 (GND), USB1.A1_B12 (A1/B12/GND), USB1.B1_A12 (B1/A12/GND), USB1.S1, USB1.S2, USB1.S3, USB1.S4; also elsewhere on the board
unnamed: R9.2, U5.C1 (MODE)
unnamed: R1.2, USB1.A5 (A5/CC1)
unnamed: R2.1, USB1.B5 (B5/CC2)
P1.14/AIN7_VBAT: R5.1, R6.2; also elsewhere on the board
P1.15/VBAT_EN: U2.B2 (EN); also elsewhere on the board
SAMD11_3V3: C6.1, U3.1 (OUT); also elsewhere on the board
SAMD11_USB_DN: USB1.A7 (A7/DN1), USB1.B7 (B7/DN2); also elsewhere on the board
SAMD11_USB_DP: USB1.A6 (A6/DP1), USB1.B6 (B6/DP2); also elsewhere on the board
TYPE-C_5V: C1.1, C2.1, C5.1, C26.1, D1.2, D4.1, Q1.1 (G), R3.2, U1.A2 (VIN), U3.3 (EN), U3.4 (IN), USB1.A4_B9 (A4/B9/VBUS), USB1.B4_A9 (B4/A9/VBUS)
VBAT: C3.1, Q1.3 (D), TP9.1 (T), U1.A1 (BAT), U2.A2 (VIN)
VBUS: C9.1, D4.2, Q1.2 (S), U5.B1 (VIN), U5.C2 (EN); also elsewhere on the board
VSYS_3V3: C10.1, L1.2, U5.A2 (VOS); also elsewhere on the board

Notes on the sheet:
I max=600mA
ICharge = 24000/120K = 200mA
Battery charge
I max=250mA
Battery voltage detection
3.3V power supply only provided for SAMD11
Battery voltage=ADC sampling voltage*2.0
User Power input:
SAMD11 IC power 3.3V
TYPE C input/output:
System 3.3V
Charging: LED Blink Charged: LED lights up for 51.2s and then goes off

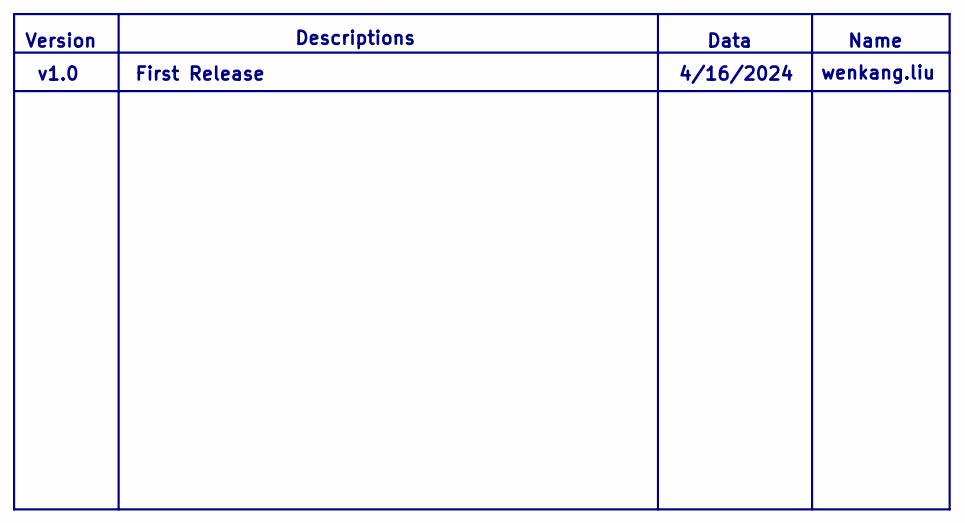
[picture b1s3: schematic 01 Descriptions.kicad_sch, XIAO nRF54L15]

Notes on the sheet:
4/16/2024
Version
Name
v1.0
First Release
Data
wenkang.liu
Descriptions

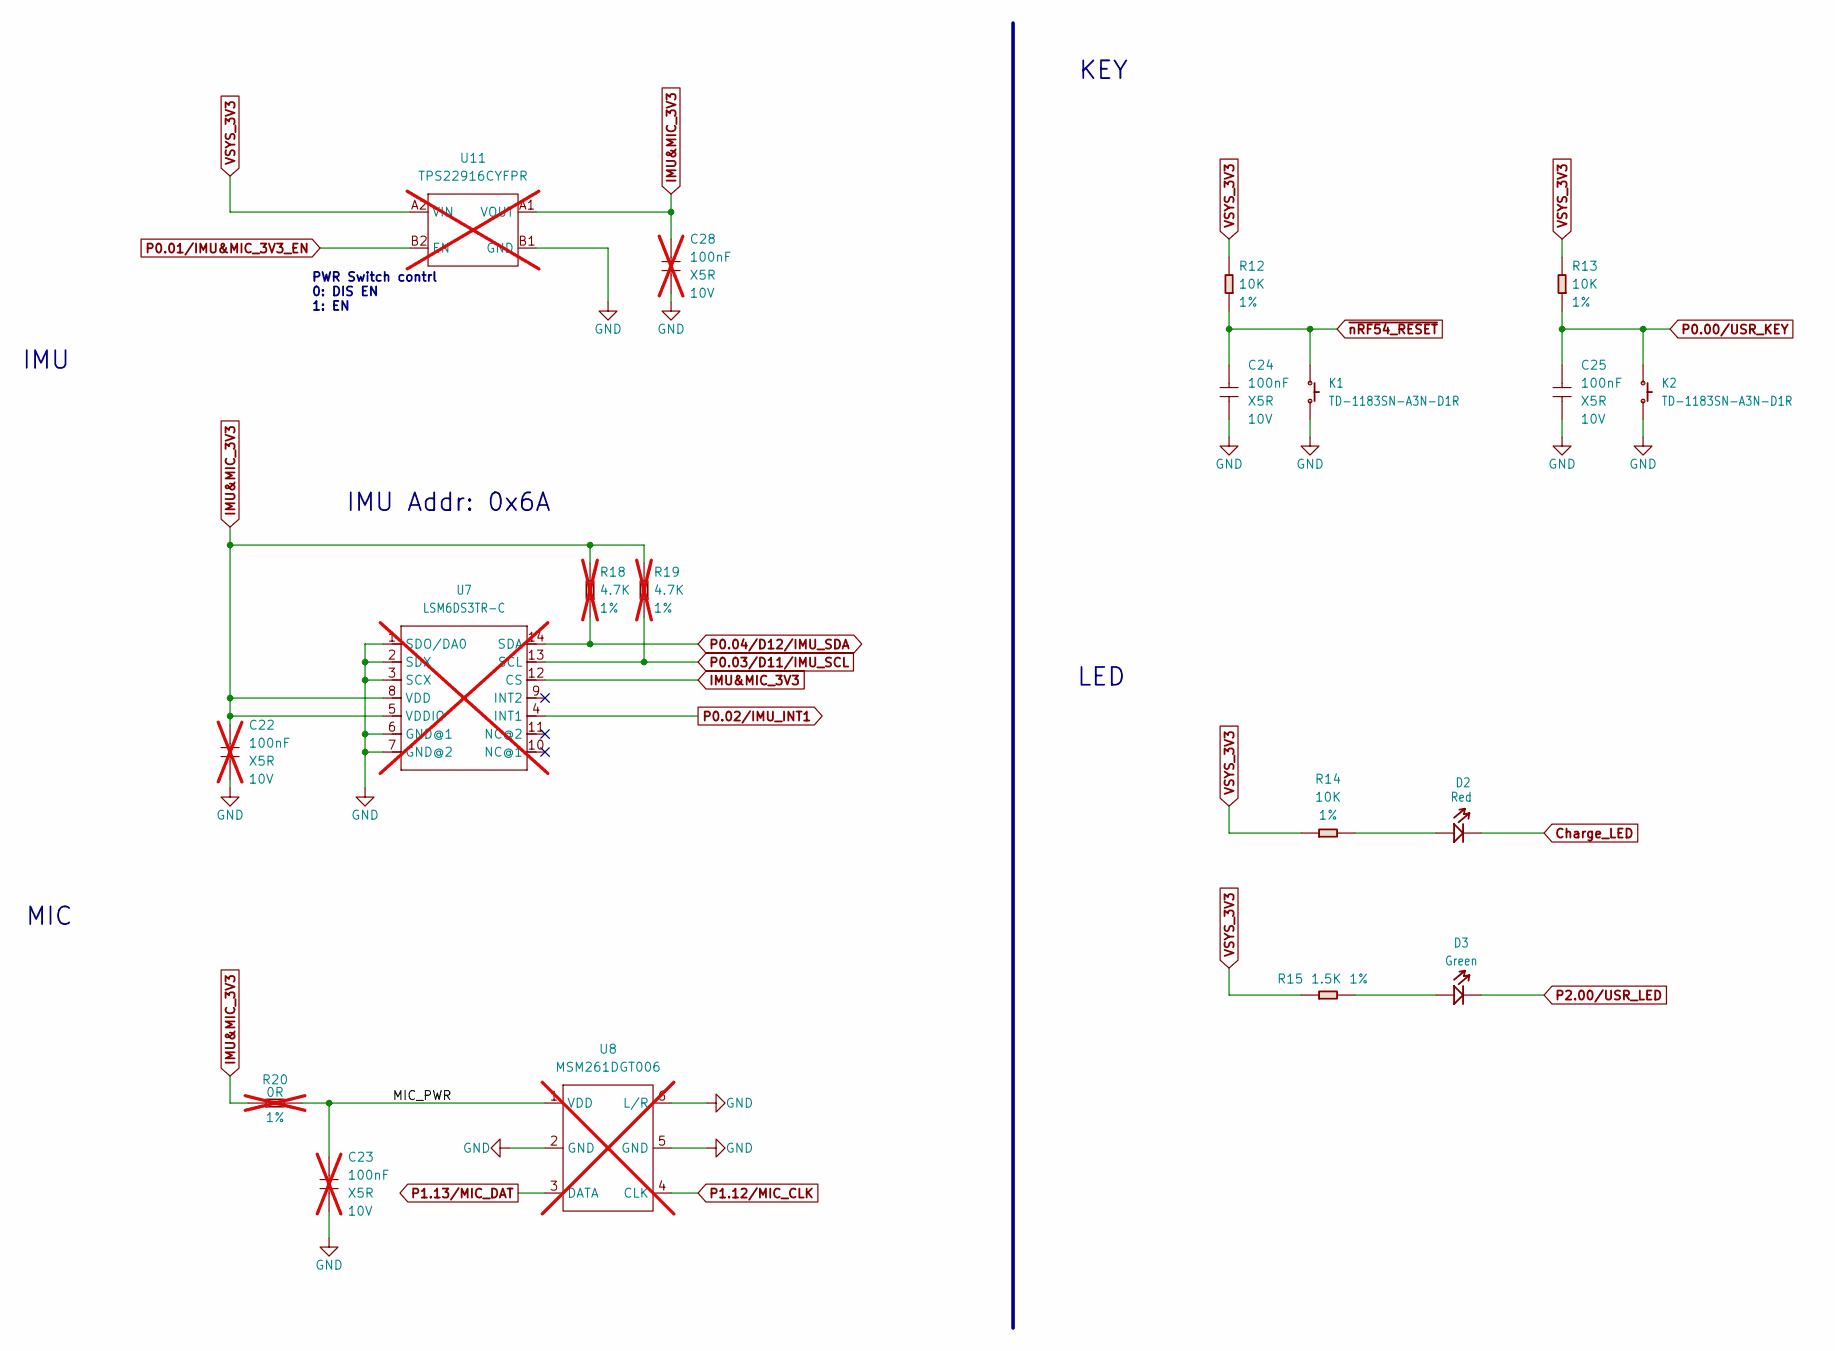
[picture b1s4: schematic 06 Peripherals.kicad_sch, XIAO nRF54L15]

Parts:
C22, C23, C28: 100nF; C0201; Voltage Rating 10V; MPN CC0201KRX5R6BB104; not fitted
C24, C25: 100nF; C0201; Voltage Rating 10V; MPN CC0201KRX5R6BB104
D2: Red; LED-0402; MPN BL-HUB37A-AV-TRB
D3: Green; LED-0402; MPN BL-HGE37A-AV-TRB
K1, K2: TD-1183SN-A3N-D1R; BUTTON_TD1183SA; MPN TD-1183SN-A3N-D1R
R12, R13, R14: 10K; R0201; Power Rating 1%; MPN RC0201FR-0710KL
R15: 1.5K; R0201; Power Rating 1%; MPN RC0201FR-071K5L
R18, R19: 4.7K; R0201; Power Rating 1%; MPN RC0201JR-074K7L; not fitted
R20: 0R; R0201; Power Rating 1%; MPN RC0201FR-070RL; not fitted
U7: LSM6DS3TR-C; LGA14-0.5-2.5X3X0.86MM; MPN LSM6DS3TR-C; not fitted
U8: MSM261DGT006; MIC6P-0.94-4X2X1.1MM; MPN MSM261DGT006; not fitted
U11: TPS22916CYFPR; WLCSP4-0.4-0.77X0.77X0.33MM; MPN TPS22916CYFPR; not fitted

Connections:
/06 Peripherals/MIC_PWR: C23.1, R20.2, U8.1 (VDD)
Charge_LED: D2.2 (-); also elsewhere on the board
GND: C22.2, C23.2, C24.2, C25.2, C28.2, K1.2, K2.2, U7.1 (SDO/DA0), U7.2 (SDX), U7.3 (SCX), U7.6 (GND@1), U7.7 (GND@2), U8.2 (GND), U8.5 (GND), U8.6 (L/R), U11.B1 (GND); also elsewhere on the board
IMU&MIC_3V3: C22.1, C28.1, R18.2, R19.2, R20.1, U7.5 (VDDIO), U7.8 (VDD), U7.12 (CS), U11.A1 (VOUT)
unnamed: D2.1 (+), R14.2
unnamed: D3.1 (+), R15.2
P0.00/USR_KEY: C25.1, K2.1, R13.1; also elsewhere on the board
P0.01/IMU&MIC_3V3_EN: U11.B2 (EN); also elsewhere on the board
P0.02/IMU_INT1: U7.4 (INT1); also elsewhere on the board
P0.03/D11/IMU_SCL: R19.1, U7.13 (SCL); also elsewhere on the board
P0.04/D12/IMU_SDA: R18.1, U7.14 (SDA); also elsewhere on the board
P1.12/MIC_CLK: U8.4 (CLK); also elsewhere on the board
P1.13/MIC_DAT: U8.3 (DATA); also elsewhere on the board
P2.00/USR_LED: D3.2 (-); also elsewhere on the board
VSYS_3V3: R12.2, R13.2, R14.1, R15.1, U11.A2 (VIN); also elsewhere on the board
~nRF54_RESET: C24.1, K1.1, R12.1; also elsewhere on the board

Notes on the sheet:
IMU Addr: 0x6A
LED
MIC
KEY
IMU
PWR Switch contrl 0: DIS EN 1: EN

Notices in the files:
README.md:
Project license: [CC0-1.0 / Public Domain](LICENSE). Third-party notices: [THIRD_PARTY_NOTICES.md](THIRD_PARTY_NOTICES.md).
